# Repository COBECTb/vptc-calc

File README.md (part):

# Калькулятор ВПТК (Волновой редуктор с промежуточными телами качения)

## Сохранённая плата энкодера

Текущая электрическая плата **CAN V2.4 / D70** находится в [electronics/encoder_can_v2](electronics/encoder_can_v2/README.md). Это фиксированный вариант под конкретную геометрию редуктора Ø70 мм, подшипник 40×52×7 мм и фазу сборочных отверстий 39°. Она имеет четыре слоя и толщину 0,8 мм; варианты другой толщины или с двумя слоями не входят в эту ревизию. Размерная привязка и параметры эталонной сборки — [MECHANICAL_VARIANT.md](electronics/encoder_can_v2/MECHANICAL_VARIANT.md).

## Запуск

Основной `calc-vpts.py` создаёт **полный комплект CAD**: сборки, отдельные
печатные детали, библиотеки геометрии и список деталей. Для текущего Ø70:

```sh
python3 calc-vpts.py --resolution 600 --ratio 19 --roller-d 4 --roller-h 5 \
  --rout 28 --diameter 70 --part knee_assembly \
  --output output/generated/robot.scad
```

Требуется Python с `numpy`. Результат:

- `robot.scad` — общий файл; `generated_part` выбирает сборку или деталь;
- `robot_assets/` — все необходимые библиотеки, включая текущую стопу;
- `robot_print/` — **37 отдельных заданий** с названиями деталей;
- `robot_print/README.md` — количество на узел, материалы и порядок сборки;
- `robot.encoder.json` — размеры, совместимость PCB, перечень деталей и хеши файлов.

Все эти файлы генерируются одним запуском. `--part` выбирает начальное отображение,
а не ограничивает состав комплекта. Папки `robot_assets` и `robot_print` должны
переноситься вместе с `robot.scad`; сохранённых STL или моделей из `output` для
работы генератора не требуется. При повторной генерации нужен `--overwrite`;
защищён каждый файл комплекта, включая библиотеки и отдельные задания печати.

Чтобы сразу получить STL всех печатных вариантов, добавить `--export-stl` к команде.
Нужен установленный OpenSCAD; путь можно передать через `--openscad`. Для отдельных
STL добавить, например, `--export-stl --stl-part encoder_magnet_ring_half --stl-part knee_magnet_ring`.
Файлы появятся рядом с соответствующими SCAD. Исходные варианты и запасные детали
включены в каталог отдельно: печатать весь каталог как комплект одной ноги не нужно.
Количество указано **на узел**, а не на всю собаку; `assemblies` в JSON группирует
детали по назначению.

Автоматический экспорт использует двоичный STL и проверяет замкнутость сетки
и направление граней. Численные вырождения экспорта устраняются с округлением
не более 0,00001 мм; если сетка остаётся незамкнутой, экспорт завершается ошибкой.
Подробности рендера и проверки сохраняются в `*_print/.build/`.

Для правок использовать `calc-vpts.py`, `encoder_scad.py` и исходники в
[`cad/`](cad/README.md), затем повторять генерацию. В `cad/` перенесены принятые
модели редуктора V2, колена с двумя опорами полукольца и текущей стопы.
Для штатного Ø70 плата загружается из сохранённых механических данных KiCad V2;
хеш исходной PCB проверяется перед генерацией. Для другого диаметра рассчитывается
механический вариант редуктора; готовая PCB V2 и колено автоматически не масштабируются.

В исходной механике остаётся осевое пересечение ушка тяги и короткого плеча
шарнира на 0,5 мм. Генератор его сохраняет; это нужно исправить до сборки.
Перенос моделей в генератор не является подтверждением прочности или точности энкодера.

Альтернатива — Docker (с OpenSCAD для экспорта STL):

```
docker build -t vptc-calculator .
```

```
docker run --rm -it \
  -v "$(pwd)":/app -w /app \
  vptc-calculator
```

## Описание

Калькулятор генерирует 3D-модель волнового редуктора с роликами (VPTC - Variable Pace Traction Coupling) с параметрами, задаваемыми пользователем. В папку output помещается файл vptc_roller.scad который необходимо открыть в программе OpenSCAD.

Существующие файлы защищены от перезаписи. Для нового результата укажите `--output`,
а для намеренной перезаписи выбранного файла — `--overwrite`.

### Варианты деталей редуктора для установки энкодера

Для установки абсолютного энкодера предусмотрены доработанные варианты
крышки редуктора, зажима соединителей и обоих соединителей, а также защитная
накладка крышки. Плата и носитель магнитов входят в эту сборку как компоненты
энкодера. Исходные модули деталей и режим `legacy` сохранены. Пример без
интерактивного ввода:

```sh
python calc-vpts.py --resolution 600 --ratio 19 --roller-d 4 --roller-h 5 \
  --rout 28 --diameter 70 --part encoder_assembly \
  --output output/encoder_reducer_generated.scad
```

Рядом сохраняется `*.encoder.json`: размеры колец, положение датчиков/крепежа,
контур платы и осевые размеры для будущей генерации платы. Ни один файл ручных
вариантов в `output` генератор не читает и не изменяет.

Доступные значения `--part`:

| Значение | Результат |
| --- | --- |
| `legacy` | Исходная сборка и модули робота |
| `encoder_assembly`, `encoder_section`, `encoder_exploded` | Сборка, разрез, разнесённая сборка |
| `encoder_cap`, `encoder_lid`, `encoder_print` | Крышка редуктора под энкодер, её защитная накладка, обе детали для печати |
| `encoder_clamp`, `encoder_clamp_half` | Доработанный зажим соединителей под энкодер, одна печатная половина |
| `encoder_magnet_ring`, `encoder_clamp_print` | Отдельные половинки кольца со сквозными отверстиями, две половины стоя и обе половинки кольца плашмя |
| `encoder_connector`, `encoder_load_connector` | Выходной соединитель и соединитель нагрузки редуктора, доработанные под энкодер |
| `encoder_pcb` | Механический контур платы |
| `reducer_complete` | Полный редуктор с крышкой V2, сепаратором, подшипниками и соединителями |
| `leg_assembly` | Нога с текущим коленом V2 и стопой; анимация в пределах проверенного хода колена |
| `knee_assembly`, `knee_section`, `knee_exploded` | Сборка колена, разрез и разнесённый вид |
| `knee_mount`, `knee_stage` | Две опоры полукольца и этапы сборки колена |
| `knee_hip`, `knee_lower`, `knee_shin`, `knee_cover`, `knee_magnet_ring` | Печатные детали колена с платой V2 |
| `encoder_magnet_ring_half` | Одна одинаковая половинка кольца редуктора для печати плашмя |
| `foot_rigid`, `foot_sole`, `foot_cuff` | Текущая стопа с зажимом, TPU-накладка и запасной зажим |
| `body_front`, `body_rear`, `body_battery` | Отдельные секции корпуса робота |

В OpenSCAD выбор можно менять переменной `generated_part`. Все варианты редуктора Ø70
по умолчанию используют угол основных отверстий **39°**, чтобы совпасть с текущей
KiCad-платой и взаимно соответствовать в одном комплекте. Явный `--hole-angle` задаёт
свой угол; генератор предупреждает, если готовая плата Ø70 ему не соответствует.

Колено: `animate=false` включает ручное управление `knee_angle`; при `animate=true`
работает OpenSCAD **Вид → Анимировать**. При `$t=0` отображается заданный угол.
Печатные задания не двигаются при анимации. `legacy` сохраняет прежнюю компоновку
робота, заменяя зависимости от внешних STL процедурными модулями; новые колено
и полная нога представлены отдельными режимами.

Количество магнитов выбирается как максимальная чётная пара при перемычке не менее
0,6 мм между посадками Ø5,2. Внутреннее кольцо содержит на одну пару полюсов меньше:
для Ø70 получается **24/26**, для Ø80 — **30/32**. Радиусы, длина шейки и осевой подъём
вычисляются из размеров: в текущем Ø70 сепаратор и подшипник подняты на 0,5 мм,
шейка соединителя имеет длину **6,75 мм**.
Магнитные посадки вынесены в отдельное кольцо толщиной **0,8 мм** со
сквозными отверстиями Ø5,2, которое печатается двумя одинаковыми половинками
плашмя — по одной на каждую половину зажима. Плоский торец полузажима снижен
с Z12 до Z11,6; верхняя стенка стала тоньше на 0,4 мм. Кольцо занимает
Z11,6–12,4, поэтому положение магнитов и длины соединителей сохранены.
Печатаются две одинаковые половины корпуса зажима и две одинаковые половинки
кольца. Половинку приклеивают к торцу своей половины зажима; толщину клеевого
слоя нужно учитывать при установке.
Для отдельной печати одной половинки есть
`output/connector_clamp_magnet_ring_half_0p8.scad` (нужно два экземпляра).
В каждой половинке Ø70 — 12 внутренних и 13 наружных отверстий. Пластик одинаковый,
но полярность первого магнита наружного ряда у второй половинки противоположная;
у внутреннего ряда — одинаковая. Чередование N/S сохраняется через оба стыка.
Произвольный общий поворот собранного зажима учитывается привязкой к известному
положению сустава (упор или сборочный шаблон) с сохранением смещения нуля.
После переустановки зажима эту привязку повторяют. Установочные метки либо
однозначный механический упор полезны для повторяемости сборки; они не заменяют
проверку погрешности энкодера. Неправильную полярность отдельных магнитов одной
поправкой нуля исправить нельзя.
Под максимальный корпус MCU 5,1×5,1 мм предусмотрен локальный карман с зазором
0,2 мм по сторонам и 0,15 мм снизу. Для Ø70 дно кармана находится на Z10,25,
выше неизменённого подшипникового упора Z10.

Для штатного Ø70 генератор использует контур, два крепления и компоненты
разведённой компактной платы V2 (`electronics/encoder_can_v2`). Механические данные
читаются из `design/mechanics_v2.json`; хеш проверяется по сохранённой PCB.
Экспорт обновляется `scripts/export_mechanics.py` через Python KiCad.
Актуальная воспроизводимая сборка крышки — режим `encoder_assembly` основного генератора.
Сохранённый прежний файл: `output/reducer_cap_encoder_can.scad`.
Для других диаметров плата в генерируемом SCAD остаётся механическим макетом.
Другой диаметр или расположение отверстий требует новой электрической разводки. Подъём сепаратора ещё требует
проверки его окон роликов и сопряжения с 688ZZ в полной сборке редуктора.
У открытых поверхностей вычитания выступают на 0,01 мм; глухие глубины и упор
подшипника сохранены.

Проверки генератора: `python -m unittest discover -s tests -v`. Если установлен
OpenSCAD, они также проверяют компиляцию всех новых вариантов Ø70/Ø80 и реальную
геометрию упора подшипника, дна потая и локального кармана MCU.
Путь CLI можно задать переменной `OPENSCAD`.

## Генерируемые детали

Иллюстрированный каталог ниже показывает **29 ранее сохранённых деталей**.
Актуальный полный перечень, включая колено V2 и отдельные полукольца, создаётся
в `*_print/README.md` основным генератором.
На каждой картинке — геометрия соответствующего модуля OpenSCAD, а не эскиз.
Слева объёмный вид, справа вид вдоль локальной оси Z. Масштаб видов подбирается
отдельно; габарит XYZ указан под изображением. Размеры — в миллиметрах, углы — в градусах.

### Как получить и открыть отдельную деталь

Для каждой детали есть готовый файл в [docs/parts](docs/parts), который вызывает
ровно один модуль и скрывает остальную сборку. Ссылка «Открыть деталь» дана
в каждой карточке. Открыть этот `.scad` в OpenSCAD, нажать **F5** для просмотра,
**F6** для точного рендера, затем **Файл → Экспорт → STL**. Положение для
печати отдельно задано только там, где вызван модуль с суффиксом `_print`.

Картинки и файлы карточек используют сохранённый
[эталонный результат генератора](docs/parts/reference_model.scad):

```sh
python3 calc-vpts.py --resolution 600 --ratio 19 --roller-d 4 --roller-h 5 \
  --rout 28 --diameter 70 --hole-angle 39 --part encoder_assembly \
  --output output/my_reducer.scad
```

Для собственной версии создать рядом с результатом небольшой файл, например
`output/my_cap.scad`:

```scad
use <my_reducer.scad>
$fn=60;
cap();
```

Вместо `cap();` подставить вызов из нужной карточки. Для текущей стопы и TPU-опоры
использовать задания `foot_rigid.scad` и `foot_sole.scad` из созданного каталога `*_print/`.

### Где изменять параметры

| Уровень | Что менять | Когда пересчитывается |
| --- | --- | --- |
| CLI генератора | `--resolution`, `--ratio`, `--roller-d`, `--roller-h`, `--rout`, `--diameter`, `--hole-angle` | Повторным запуском `calc-vpts.py` с новым `--output` |
| Аргументы модулей | Например, `reducer_connector(h1=8,skirt=true)` или `shin(foot=false)` | Сразу при F5/F6 в файле отдельной детали |
| Переменные SCAD | Толщины, высоты, зазоры и размеры посадок в сгенерированном файле | После изменения самого файла, из которого импортируется модуль |
| Библиотека стопы | Переменные `h_*` в `cad/foots_h.scad` | После повторного запуска генератора |

**Профиль впадин, число роликов, координаты отверстий и часть размеров записываются
Python как готовые числа.** Одной замены `D_out` или `d_roller` в SCAD недостаточно:
для другой передачи или диаметра нужно повторно запустить генератор.
Переменные из файла, подключённого через `use`, не становятся переменными внешнего
файла: менять их нужно в исходном SCAD, а через вызов передавать только его аргументы.
Значения в таблицах ниже относятся к указанному эталону Ø70; это не универсальные
размеры для всех диаметров. Исходный генератор и его формулы — [calc-vpts.py](calc-vpts.py),
параметры доработок редуктора под энкодер — [encoder_scad.py](encoder_scad.py).

### Редуктор

#### 1. Жёсткое колесо / корпус

[Открыть деталь](docs/parts/rigid_gear.scad) · Источник: [reference_model.scad](docs/parts/reference_model.scad).

Вызов для отдельного файла:

```scad
rigid_gear();
```

Как построить: Создать цилиндр корпуса. Выдавить рассчитанный Python профиль впадин и вычесть его сверху. Вырезать отверстия A/B и ступенчатую посадку 6803ZZ.

| Параметр | Значение в эталоне | Что задаёт |
| --- | --- | --- |
| `D_out` | 70 | Наружный диаметр, из --diameter |
| `h_reducer` | 15.5 | Высота корпуса: h_roller + 10.5 |
| `h_cut` | 10 | Глубина профильной полости: h_roller + 5 |
| `--ratio / --resolution` | 19 / 600 | 20 впадин и число точек рассчитанного профиля |
| `motor_radius / motor_angles` | 32 / [54,144,234,324]° | Расположение отверстий B |

#### 2. Корпус с боковым креплением

[Открыть деталь](docs/parts/rigid_gear_with_bracing.scad) · Источник: [reference_model.scad](docs/parts/reference_model.scad).

Вызов для отдельного файла:

```scad
rigid_gear_with_bracing();
```

Как построить: Взять rigid_gear(). Добавить боковой объём, двумя овальными конусами сформировать выемки, повторно прорезать отверстия B и отверстия бокового крепления.

| Параметр | Значение в эталоне | Что задаёт |
| --- | --- | --- |
| `bracing_offset_y` | 29 | Смещение крепления: D_out/2 − 6 |
| `bracing_offset_z` | 17.5 | Высота оси крепления: D_out/4 |
| `bracing_offset_x` | 2.2 | Значение в сгенерированном SCAD; 2.25 в Python округляется до одного знака |
| `side_long / side_short` | 29.564 / 12.246 | Расстояния между боковыми отверстиями |

#### 3. Сепаратор

[Открыть деталь](docs/parts/separator.scad) · Источник: [reference_model.scad](docs/parts/reference_model.scad).

Вызов для отдельного файла:

```scad
separator();
```

Как построить: Создать цилиндр Rsep_out, вычесть внутреннюю полость Rsep_in. Сделать ступени фланца, посадку 688ZZ, радиальные окна под ролики и восемь крепёжных отверстий.

| Параметр | Значение в эталоне | Что задаёт |
| --- | --- | --- |
| `Rsep_m` | 25.2 | Радиус центров роликов |
| `Rsep_out / Rsep_in` | 26.08 / 24.32 | Наружный и внутренний радиусы сепаратора |
| `separator_h` | 9 | Основная высота: h_roller + 4 |
| `bearing_inner / bearing_outer` | 40 / 52 | Посадка выбранного 6808-2RS |
| `--ratio / h_roller` | 19 / 5 | Число окон / высота роликов |

#### 4. Ролики

[Открыть деталь](docs/parts/rollers.scad) · Источник: [reference_model.scad](docs/parts/reference_model.scad).

Вызов для отдельного файла:

```scad
rollers();
```

Как построить: Построить цилиндр ролика с центром по Z. Разместить 19 копий на окружности Rsep_m поворотами с шагом 360/19.

| Параметр | Значение в эталоне | Что задаёт |
| --- | --- | --- |
| `d_roller / h_roller` | 4 / 5 | Диаметр / высота, из --roller-d и --roller-h |
| `Rsep_m` | 25.2 | Радиус расположения |
| `--ratio` | 19 | Количество роликов; пересчитывается в Python |

#### 5. Эксцентрик

[Открыть деталь](docs/parts/eccentric.scad) · Источник: [reference_model.scad](docs/parts/reference_model.scad).

Вызов для отдельного файла:

```scad
eccentric();
```

Как построить: Создать диск радиуса rd. Вырезать проход Ø24 и посадку под 6803ZZ Ø26, оставив нижний упор. Смещение оси задаётся при установке детали в сборку.

| Параметр | Значение в эталоне | Что задаёт |
| --- | --- | --- |
| `rd` | 23.2 | Радиус диска; вычисляется и записывается в геометрию |
| `eccentric_h` | 7 | Толщина: h_roller + 2 |
| `eccentricity` | 0.8 | Смещение в сборке: 0.2 × d_roller |
| `посадка 6803ZZ` | Ø26 × 5 | Геометрия подшипника; Ø24 у нижнего упора |

#### 6. Вал эксцентрика

[Открыть деталь](docs/parts/eccentric_shaft.scad) · Источник: [reference_model.scad](docs/parts/reference_model.scad).

Вызов для отдельного файла:

```scad
eccentric_shaft();
```

Как построить: Объединить цилиндры основания, проставки, смещённой ступени и верхнего шипа. Вырезать осевое отверстие и два нижних паза.

| Параметр | Значение в эталоне | Что задаёт |
| --- | --- | --- |
| `ecc_shaft_h1` | 5 | Высота нижней ступени |
| `ecc_spacer_h` | 2.5 | Высота проставки |
| `ecc_shaft_h2` | 6 | Высота смещённой ступени |
| `ecc_pin_h` | 6 | Высота шипа Ø8 |
| `eccentricity` | 0.8 | Смещение средней ступени по X |

#### 7. Крышка редуктора

[Открыть деталь](docs/parts/cap.scad) · Источник: [reference_model.scad](docs/parts/reference_model.scad).

Вызов для отдельного файла:

```scad
cap();
```

Как построить: Создать диск D_out. Вырезать посадку наружного кольца подшипника, сквозное отверстие меньшего диаметра, нижнюю полость под сепаратор и отверстия A с потаями.

| Параметр | Значение в эталоне | Что задаёт |
| --- | --- | --- |
| `cap_thickness` | 11 | Общая толщина |
| `bearing_outer` | 52 | Диаметр посадки 6808-2RS |
| `bearing_width` | 7 | Ширина выбранного подшипника |
| `Rsep_out` | 26.08 | Радиус нижней полости = Rsep_out + 1 |
| `--hole-angle` | авто / 39° для энкодера Ø70 | Фаза группы A задаётся при генерации |

#### 8. Крышка с боковым креплением

[Открыть деталь](docs/parts/cap_with_bracing.scad) · Источник: [reference_model.scad](docs/parts/reference_model.scad).

Вызов для отдельного файла:

```scad
cap_with_bracing();
```

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
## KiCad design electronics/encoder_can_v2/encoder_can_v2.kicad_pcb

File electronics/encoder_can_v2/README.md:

# Энкодер CAN V2.4 — вариант для редуктора D70

**Сохранённый размерный вариант: `encoder_can_v2_4_d70`.** Эта готовая плата рассчитана на конкретную сборку ВПТК Ø70 мм: подшипник 40×52×7 мм, основные отверстия на R31,5 мм с фазой 39°, магнитные дорожки R23,5/R29,5 мм. Для другого редуктора совместимость определяется повторной проверкой геометрии; изменение диаметра в калькуляторе не масштабирует готовую разводку. Полная привязка и параметры воспроизведения — [MECHANICAL_VARIANT.md](MECHANICAL_VARIANT.md).

Открыть `encoder_can_v2.kicad_pro` в KiCad 10. Четыре слоя, 0,8 мм; возвращён **точный исходный узкий контур**, до расширения под отступ 1 мм. Габарит в локальной радиально-поперечной системе **16,853 × 42,938 мм**, площадь контура до вычитания крепёжных NPTH **395,29 мм²**. Наружный радиус 33,4 мм. Все 826 отрезков Edge.Cuts независимо сверены с сохранённой исходной платой.

**U2/U3 не перемещались:** центры KiCad (123,2666;95,9099) и (129,1928;94,9713) мм, ориентация 9°. Активные точки рассчитаны на кольца R23,5/R29,5 мм. J2 также сохранён. Монтажные отверстия PCB в локальных координатах (26,92;−9,605) и (28,1933;9,6043) мм. Оба доступа к сборочным M3 — открытые вырезы; замкнутых внутренних окон контура нет. Актуальный контур и крепления передаются в OpenSCAD.

F.Cu: Hall, CAN, защита и LDO. In1.Cu: один связный полигон GND без сигнальных дорожек. In2.Cu: 3,3 В и сигналы. B.Cu: MCU, кварц, LED, пассивные детали и клипса. Минимальные дорожка/зазор 0,127 мм, переходы 0,4/0,2 и 0,45/0,2 мм. Все переходы сквозные, закрыты маской с обеих сторон. Номинальный минимальный отступ от края меди перехода до любой паяемой площадки обеих сторон, включая свою цепь и J1/J2, — **0,505 мм** (требование ≥0,5 мм). Под максимальными корпусами переходов нет; минимальный номинальный зазор до корпуса 0,125 мм. 14 прямых выходов MCU чередуются по длине: 11 реальных межслойных переходов и 3 поворота на той же стороне без лишнего отверстия. Изготовительные допуски не включены в эту номинальную величину.

Питание: стабилизированные **5 В**. J1: 1 +5 В, 2 GND, 3 CANH, 4 CANL; ручная пайка проводов. J2 на B.Cu: **+5 В вход, GND, SWDIO, SWCLK, NRST**, 5 площадок P2.54. Pin1 не VTREF; логика SWD 3,3 В. Программировать до установки платы в корпус. Подробности — [PROGRAMMING.md](PROGRAMMING.md).

STM32G431KBU6, два TMAG5273A2QDBVR на независимых I²C, TCAN332GDCNR, TPS7A2033PDBVR. D1 — защита CAN PESD5V0S2BT,215. Кварц — точный ABM10-16.000MHZ-12-R80-3-D30-T. R9 120 Ом по умолчанию DNP, устанавливается только на двух концах всей шины.

D2 зелёный — питание 3,3 В, D3 жёлтый — команды, D4 красный — фаза. Последние два управляются PA4/PA5; прошивка индикаторов ещё требуется. Корпуса Kingbright APG1005 ограничены высотой 0,3 мм. Прозрачные световоды редуктора Ø0,6 мм в каналах Ø0,8 мм — опытная конструкция: изготовление и яркость требуют пробной сборки. В колене LED видны через отверстия крышки.

Под головками M2 нет наружной меди в Ø4,4 мм. Крепёж платы: **M2×5, головка не больше Ø3,8×1,3 мм, без шайбы**. Минимальный номинальный запас головки до края PCB с учётом люфта стержня — 0,7557 мм. Для сборочных M3 ISO10642 предусмотрен потай Ø7,1 мм под головку до Ø6,72×1,86 мм; длина винта выбирается по фактической полной сборке.

Механика генерируется из `calc-vpts.py`, актуальной сохранённой PCB и `cad/`, без использования старых STL. Пакет генератора содержит все печатные детали и установки платы в редукторе и колене. Для других диаметров генерация механики параметрическая; готовая электрическая PCB V2.4 рассчитана на текущую геометрию D70 и не масштабируется автоматически.

Подробной 3D-модели MCU в KiCad нет; при проверке установки OpenSCAD использует его максимальный габарит. Это не отсутствие компонента в BOM или монтаже.

Текущие проверки и условия передачи в производство — [ORDER_READINESS.md](ORDER_READINESS.md). Архив KiCad содержит местные библиотеки, STEP-модели, BOM, координаты и отчёты; в копии меняются только ссылки на модели. Производственные файлы предназначены для опытной партии. Подтверждённой точности угла, запуска кварца, теплового режима и работы всей CAN-сети без собранного образца нет.

Источник PCB SHA256: `43237adbcdb743c33c8f1bdc61387ee4b917825291ee4f41e4ae68c7d174684c`.

Шелкография V2.4: печатаемые штрихи не тоньше 0,15 мм, видимый текст не ниже 1 мм. Необязательные рамки неполярных 0402 убраны; pin 1 и обозначения Hall сохранены. Проверка учитывает опубликованные ограничения Резонит; заводское согласование стека, панели и процесса остаётся отдельным условием.

Очистка V2.4: убраны лишние петли и мелкие изломы. Сравнения до/после — `design/cleanup_details_1.png`–`cleanup_details_3.png`; реальная открытая медь — `design/mask_review.png`. Обязательная центральная паяемая площадка GND STM32 сохранена. Подробности — [design/cleanup_review.md](design/cleanup_review.md).

У U1 убран обход GND16 вокруг питания15 к GND14: оба земляных контакта подключены внутрь к EP33. Сравнение — `design/u1_ground_review.png`.

Вход внешней GND в контакт14 U1 выровнен по центру площадки; выступ над площадкой убран. Сравнение — `design/u1_entry_review.png`.

Последние зелёные правки применены: R5/BOOT0, подвод C8, ствол питания C4/C5/U2. См. `design/green_marks_review.png` и `design/green_marks_front_back.png`.

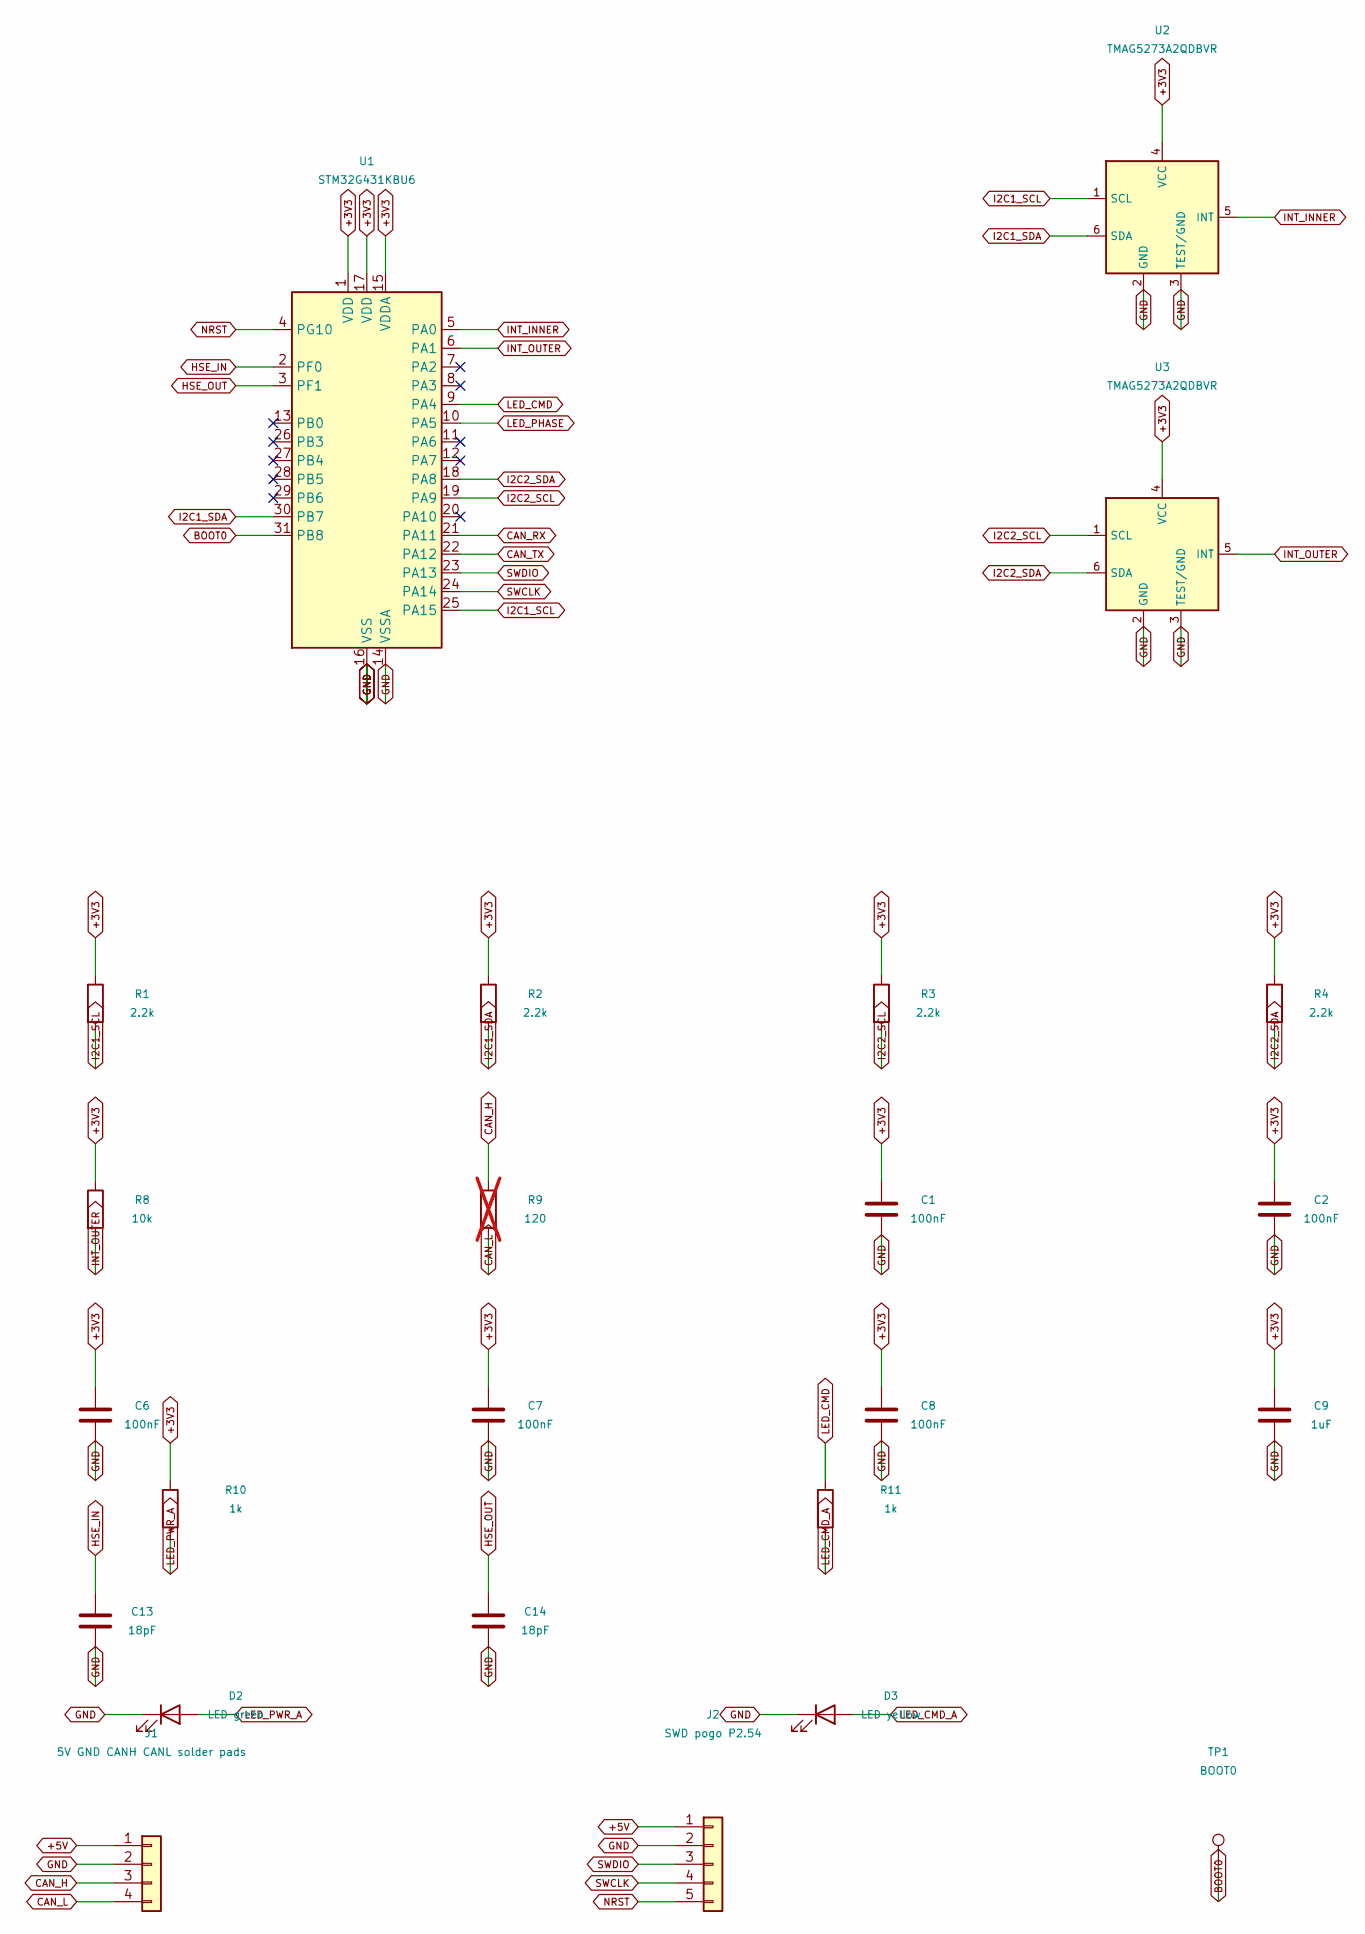
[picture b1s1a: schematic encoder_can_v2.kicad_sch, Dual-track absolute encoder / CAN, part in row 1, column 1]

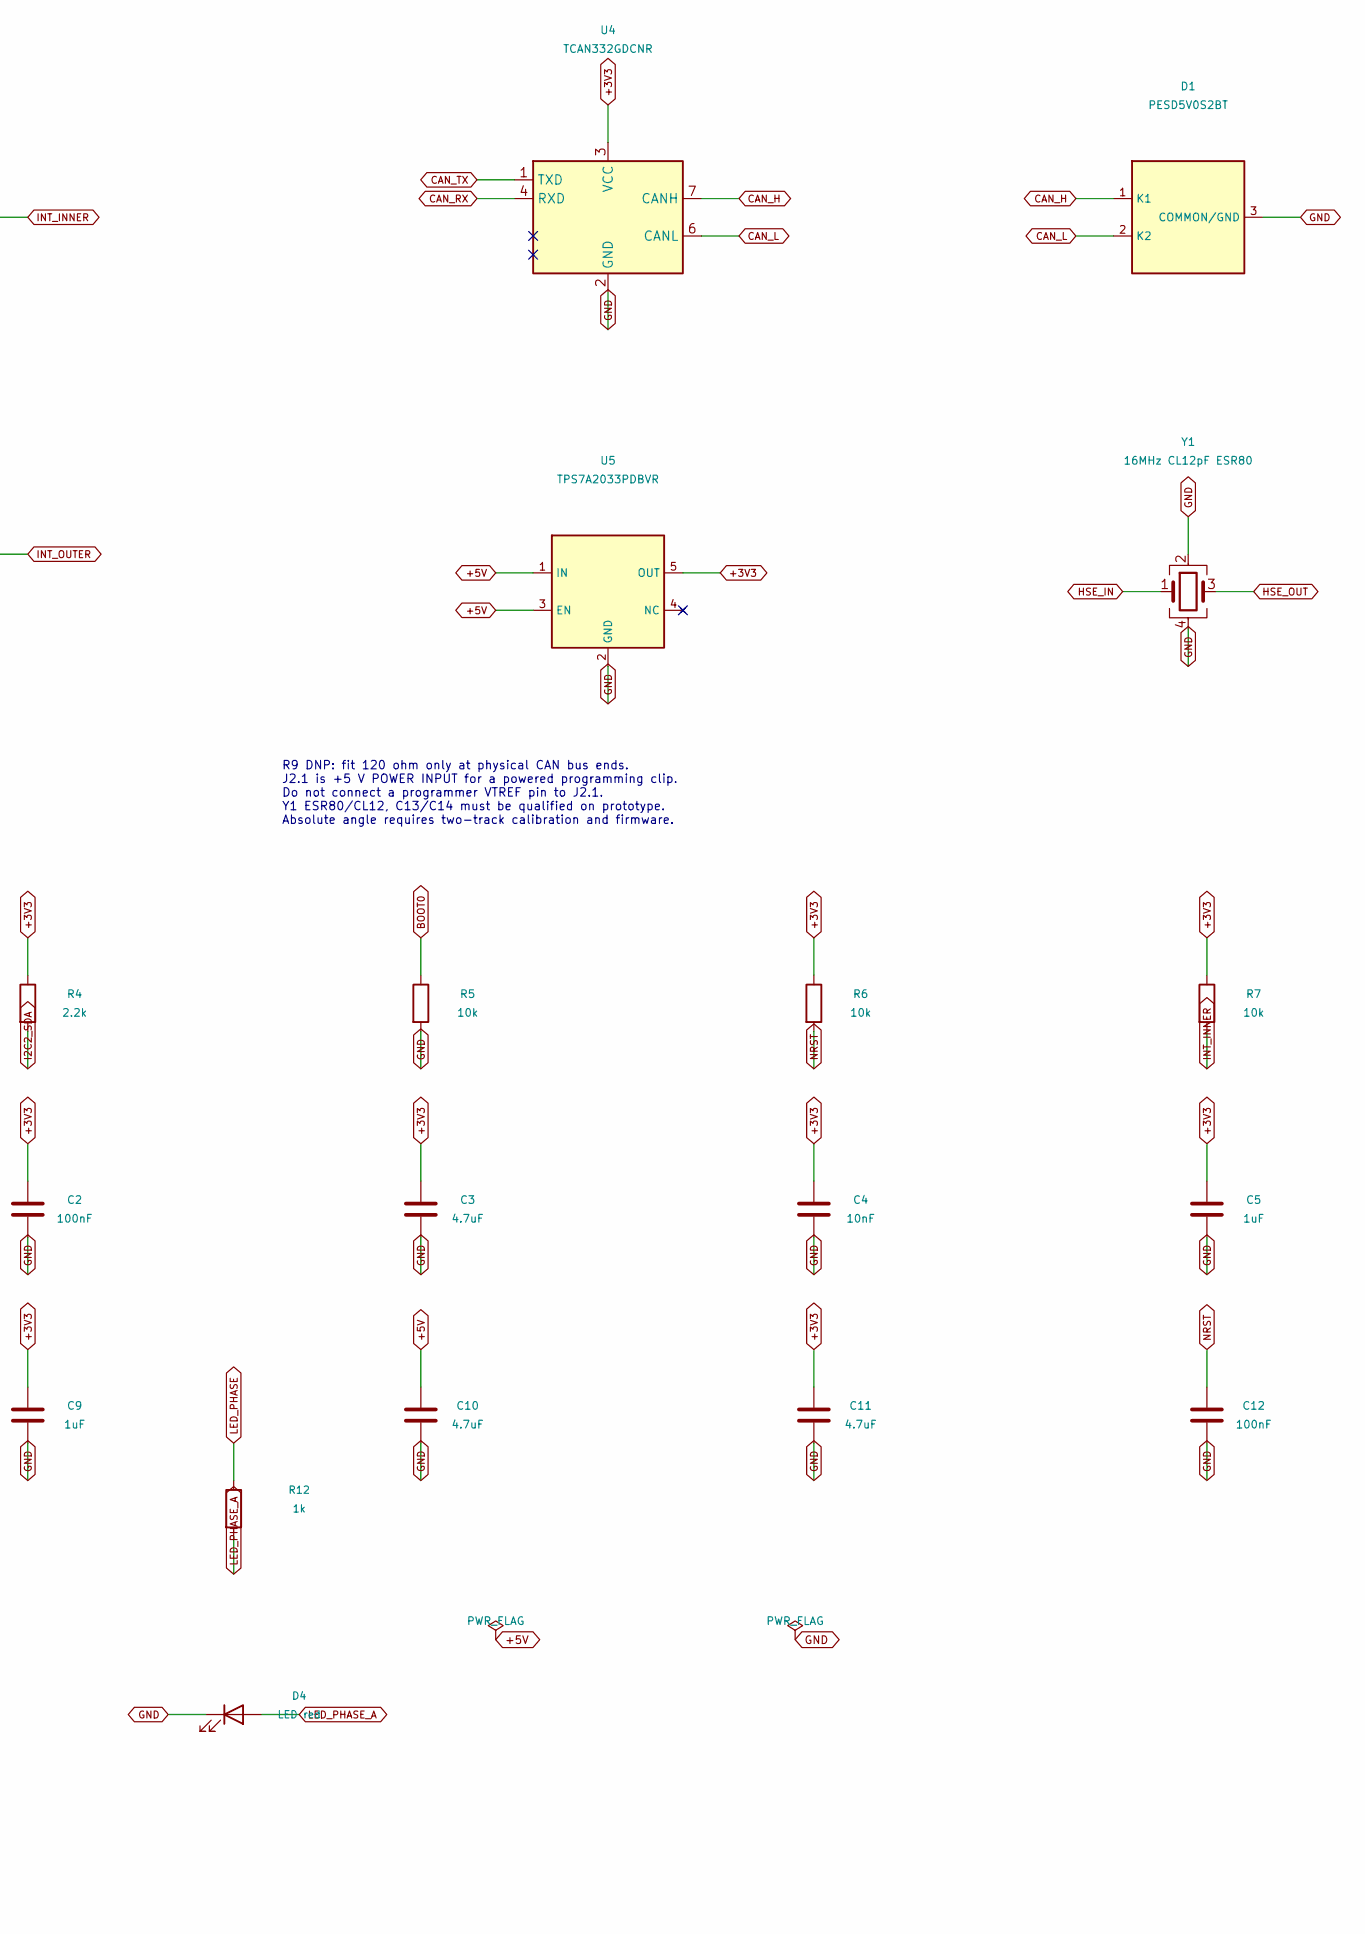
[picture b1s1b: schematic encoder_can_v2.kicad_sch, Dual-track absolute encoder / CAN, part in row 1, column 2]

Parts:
C1, C2, C6, C7, C8, C12: 100nF; C_0402_1005Metric; MPN GRM155R71C104KA88D
C3, C10, C11: 4.7uF; C_0603_1608Metric; MPN GRM188R61C475KE11D
C4: 10nF; C_0402_1005Metric; MPN GRM155R71H103KA88D
C5, C9: 1uF; C_0402_1005Metric; MPN GRM155R61E105KA12D
C13, C14: 18pF; C_0402_1005Metric; MPN GRM1555C1H180JA01D
D1: PESD5V0S2BT; SOT-23_TVS_CompactCourtyard; MPN PESD5V0S2BT,215
D2: LED green; LED_Kingbright_APG1005; MPN APG1005CGC-T
D3: LED yellow; LED_Kingbright_APG1005; MPN APG1005SYC-T
D4: LED red; LED_Kingbright_APG1005; MPN APG1005SEC/E-T
J1: 5V GND CANH CANL solder pads; WirePads_1x04
J2: SWD pogo P2.54; SWD_Pogo_1x05_P2.54mm
R1, R2, R3, R4: 2.2k; R_0402_1005Metric; MPN RC0402FR-072K2L
R5, R6, R7, R8: 10k; R_0402_1005Metric; MPN RC0402FR-0710KL
R9: 120; R_0603_1608Metric; MPN RC0603FR-07120RL; not fitted
R10, R11, R12: 1k; R_0402_Status; MPN RC0402FR-071KL
TP1: BOOT0; TestPoint_Pad_D1.0mm
U1: STM32G431KBU6; STM32G431KBU6_UFQFPN32; MPN STM32G431KBU6
U2, U3: TMAG5273A2QDBVR; TMAG5273_DBV_TI; MPN TMAG5273A2QDBVR
U4: TCAN332GDCNR; SOT-23-8; MPN TCAN332GDCNR
U5: TPS7A2033PDBVR; SOT-23-5; MPN TPS7A2033PDBVR
Y1: 16MHz CL12pF ESR80; Crystal_SMD_2520-4Pin_2.5x2.0mm; MPN ABM10-16.000MHZ-12-R80-3-D30-T

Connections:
+3V3: C1.1, C2.1, C3.1, C4.1, C5.1, C6.1, C7.1, C8.1, C9.1, C11.1, R1.1, R2.1, R3.1, R4.1, R6.1, R7.1, R8.1, R10.1, U1.1 (VDD), U1.15 (VDDA), U1.17 (VDD), U2.4 (VCC), U3.4 (VCC), U4.3 (VCC), U5.5 (OUT)
+5V: C10.1, J1.1, J2.1, U5.1 (IN), U5.3 (EN)
BOOT0: R5.1, TP1.1, U1.31 (PB8)
CAN_H: D1.1 (K1), J1.3, R9.1, U4.7 (CANH)
CAN_L: D1.2 (K2), J1.4, R9.2, U4.6 (CANL)
CAN_RX: U1.21 (PA11), U4.4 (RXD)
CAN_TX: U1.22 (PA12), U4.1 (TXD)
GND: C1.2, C2.2, C3.2, C4.2, C5.2, C6.2, C7.2, C8.2, C9.2, C10.2, C11.2, C12.2, C13.2, C14.2, D1.3 (COMMON/GND), D2.1 (K), D3.1 (K), D4.1 (K), J1.2, J2.2, R5.2, U1.14 (VSSA), U1.16 (VSS), U1.32 (VSS), U1.33 (VSS), U2.2 (GND), U2.3 (TEST/GND), U3.2 (GND), U3.3 (TEST/GND), U4.2 (GND), U5.2 (GND), Y1.2, Y1.4
HSE_IN: C13.1, U1.2 (PF0), Y1.1
HSE_OUT: C14.1, U1.3 (PF1), Y1.3
I2C1_SCL: R1.2, U1.25 (PA15), U2.1 (SCL)
I2C1_SDA: R2.2, U1.30 (PB7), U2.6 (SDA)
I2C2_SCL: R3.2, U1.19 (PA9), U3.1 (SCL)
I2C2_SDA: R4.2, U1.18 (PA8), U3.6 (SDA)
INT_INNER: R7.2, U1.5 (PA0), U2.5 (INT)
INT_OUTER: R8.2, U1.6 (PA1), U3.5 (INT)
LED_CMD: R11.1, U1.9 (PA4)
LED_CMD_A: D3.2 (A), R11.2
LED_PHASE: R12.1, U1.10 (PA5)
LED_PHASE_A: D4.2 (A), R12.2
LED_PWR_A: D2.2 (A), R10.2
NRST: C12.1, J2.5, R6.2, U1.4 (PG10)
SWCLK: J2.4, U1.24 (PA14)
SWDIO: J2.3, U1.23 (PA13)

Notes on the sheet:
R9 DNP: fit 120 ohm only at physical CAN bus ends. J2.1 is +5 V POWER INPUT for a powered programming clip. Do not connect a programmer VTREF pin to J2.1. Y1 ESR80/CL12, C13/C14 must be qualified on prototype. Absolute angle requires two-track calibration and firmware.

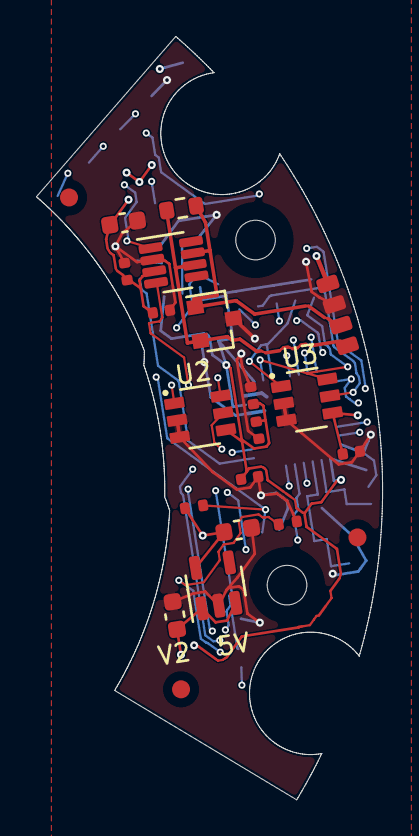
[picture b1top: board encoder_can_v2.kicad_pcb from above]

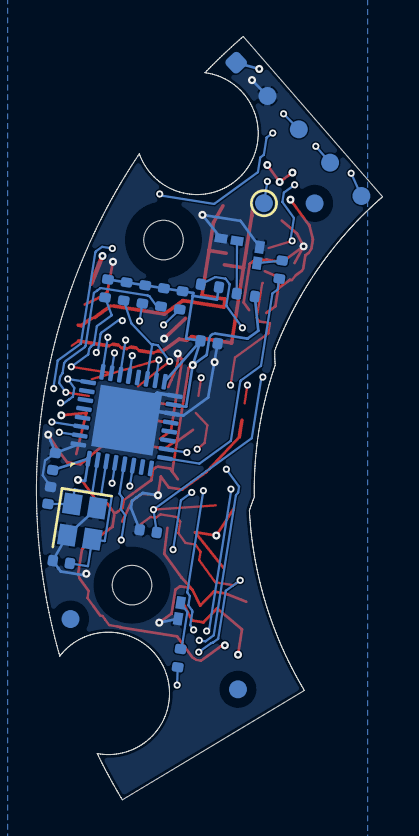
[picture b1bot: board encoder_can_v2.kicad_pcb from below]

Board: 4 copper layers, 19.2 x 42.4 mm, 47 parts (24 on the bottom side), 24 nets.

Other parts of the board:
FIDB1, FIDB2, FIDB3: Fiducial_1mm_Mask2mm
FIDF1, FIDF2, FIDF3: Fiducial_1mm_Mask2mm
H1, H2: MountingHole_2.2mm_M2; MountingHole_2.2mm_M2_LowHead

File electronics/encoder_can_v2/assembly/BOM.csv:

References,Quantity_per_board,Fitted_quantity_per_board,Value,Footprint,Manufacturer,MPN,Populate,Supplier_stock_code,Supplier,Procurement_status,Requirements
U1,1,1,STM32G431KBU6,Encoder_CAN:STM32G431KBU6_UFQFPN32,STMicroelectronics,STM32G431KBU6,Yes,C529358,LCSC,exact MPN selected; retail distributor stock observed; assembler inventory/reservation not implied,"Pin33 is KiCad EP pad numbering, not an extra perimeter lead.; No separate VBAT, VREF+, VCAP pins in this package.; VREFBUF must remain disabled because VREF+ is bonded to VDDA.; NRST remains reset input; do not configure as GPIO.; Keep SWD enabled; PA15 can become I2C1 SCL while PA13/PA14 retain SWD.; Footprint uses KiCad 10.0.6 UFQFPN32 IPC outer lands: radial center 2.4375 mm, 0.875 x 0.25 mm, pitch 0.5 mm. EP is 3.45 x 3.45 mm per ST Figure 41; adapted IPC pattern, not a literal copy of Figure 41.; maximum body height mm: 0.6"
"U2, U3",2,2,TMAG5273A2QDBVR,Encoder_CAN:TMAG5273_DBV_TI,Texas Instruments,TMAG5273A2QDBVR,Yes,C3715882,LCSC,exact MPN selected; retail distributor stock observed; assembler inventory/reservation not implied,"Official TI DBV0006A-C02 land pattern; Hall local footprint offset (-0.12,+0.40) mm. Height from seating plane 0.9 to 1.4 mm.; maximum body height mm: 1.4"
U4,1,1,TCAN332GDCNR,Package_TO_SOT_SMD:SOT-23-8,Texas Instruments,TCAN332GDCNR,Yes,C191007,LCSC,exact MPN selected; retail distributor stock observed; assembler inventory/reservation not implied,TCAN332 has neither standby nor shutdown pin; pins5/8 must be explicitly NC.; Bus absolute maximum is +/-14 V; do not substitute high-standoff automotive TVS and claim coordinated surge protection.; maximum body height mm: 1.45
U5,1,1,TPS7A2033PDBVR,Package_TO_SOT_SMD:SOT-23-5,Texas Instruments,TPS7A2033PDBVR,Yes,C2862740,LCSC,exact MPN selected; retail distributor stock observed; assembler inventory/reservation not implied,IN and EN maximum operating6 V; supply only regulated5 V.; Minimum effective COUT0.47 uF after voltage/temperature/tolerance derating.; Thermal qualification required in closed housing;300 mA rating is not a board operating-current target.; maximum body height mm: 1.45
D1,1,1,PESD5V0S2BT,Encoder_CAN:SOT-23_TVS_CompactCourtyard,Nexperia,"PESD5V0S2BT,215",Yes,C49338,LCSC,exact MPN selected; retail distributor stock observed; assembler inventory/reservation not implied,"Bidirectional +/-5 V standoff;10 V maximum clamp at1 A8/20 us,14 V at12 A.; Limits permissible CAN common-mode to about+/-5 V; shared GND is mandatory.; Transient overshoot depends on layout; this design has no certified ESD/surge immunity.; maximum body height mm: 1.1"
Y1,1,1,16MHz CL12pF ESR80,Crystal:Crystal_SMD_2520-4Pin_2.5x2.0mm,Abracon,ABM10-16.000MHZ-12-R80-3-D30-T,Yes,8063649242,ЧИП и ДИП,"Exact MPN catalogued at ChipDip 2026-10-24: MOQ1, 7–8weeks, from10 130RUB/each; no stock in Moscow shops; not reserved. Alternative8070563644 MOQ269,4weeks.","Pin1 determined by package marking/top view, not chamfer; validate supplier drawing and oscillator gain/drive before assembly release.; Load capacitors18 pF are starting values for CL12 pF and estimated3 pF stray capacitance; tune/verify startup across temperature and rails.; Exact complete MPN verified in DigiKey catalog; custom R80 option already stocked.; Body height max 0.70 mm (0.5 +0.2/-0.1), not 0.50 mm.; 1/3 crystal; 2/4 grounded case; no automatic ESR150 substitute.; maximum body height mm: 0.7; Exact R80 version; 16MHz, CL12pF, ESR<=80ohm; ESR150 is not an approved substitution"
"R1, R2, R3, R4",4,4,2.2k,Resistor_SMD:R_0402_1005Metric,YAGEO,RC0402FR-072K2L,Yes,C114762,LCSC,exact MPN selected; retail distributor stock observed; assembler inventory/reservation not implied,rated voltage V: 50; tolerance %: 1; rated power W: 0.0625; maximum body height mm: 0.4
"R5, R6, R7, R8",4,4,10k,Resistor_SMD:R_0402_1005Metric,YAGEO,RC0402FR-0710KL,Yes,C60490,LCSC,exact MPN selected; retail distributor stock observed; assembler inventory/reservation not implied,rated voltage V: 50; tolerance %: 1; rated power W: 0.0625; maximum body height mm: 0.4
R9,1,0,120,Resistor_SMD:R_0603_1608Metric,YAGEO,RC0603FR-07120RL,No,C114640,LCSC,exact MPN selected; retail distributor stock observed; assembler inventory/reservation not implied,Default DNP. Fit only if this board is a physical bus end. Use0.1 W minimum and qualify bus fault power.; rated voltage V: 75; tolerance %: 1; rated power W: 0.1; maximum body height mm: 0.55
"C1, C2, C6, C7, C8, C12",6,6,100nF,Capacitor_SMD:C_0402_1005Metric,Murata,GRM155R71C104KA88D,Yes,C71629,LCSC,exact MPN selected; retail distributor stock observed; assembler inventory/reservation not implied,dielectric: X7R; rated voltage V: 16; tolerance %: 10; maximum body height mm: 0.55
"C3, C10, C11",3,3,4.7uF,Capacitor_SMD:C_0603_1608Metric,Murata,GRM188R61C475KE11D,Yes,C77045,LCSC,exact MPN selected; retail distributor stock observed; assembler inventory/reservation not implied,dielectric: X5R; rated voltage V: 16; tolerance %: 10; maximum body height mm: 0.95
C4,1,1,10nF,Capacitor_SMD:C_0402_1005Metric,Murata,GRM155R71H103KA88D,Yes,C77019,LCSC,exact MPN selected; retail distributor stock observed; assembler inventory/reservation not implied,dielectric: X7R; rated voltage V: 50; tolerance %: 10; maximum body height mm: 0.55
"C5, C9",2,2,1uF,Capacitor_SMD:C_0402_1005Metric,Murata,GRM155R61E105KA12D,Yes,C77009,LCSC,exact MPN selected; retail distributor stock observed; assembler inventory/reservation not implied,dielectric: X5R; rated voltage V: 25; tolerance %: 10; maximum body height mm: 0.55
"C13, C14",2,2,18pF,Capacitor_SMD:C_0402_1005Metric,Murata,GRM1555C1H180JA01D,Yes,C33149,LCSC,exact MPN selected; retail distributor stock observed; assembler inventory/reservation not implied,dielectric: C0G; rated voltage V: 50; tolerance %: 5; maximum body height mm: 0.55; Initial HSE load value; characterize startup/frequency/drive on prototype
J1,1,0,5V GND CANH CANL solder pads,Encoder_CAN:WirePads_1x04,,,No,,,PCB only; do not order,
J2,1,0,SWD pogo P2.54,Encoder_CAN:SWD_Pogo_1x05_P2.54mm,,,No,,,PCB only; do not order,
TP1,1,0,BOOT0,TestPoint:TestPoint_Pad_D1.0mm,,,No,,,PCB only; do not order,
D2,1,1,LED green,Encoder_CAN:LED_Kingbright_APG1005,Kingbright,APG1005CGC-T,Yes,,,Catalogued internationally; exact low-profile MPN required. Assembler must confirm delivery/reservation.,"Top-emitting ultra-thin LED; pin1 cathode. 1k series resistor; nominal current about 1.3mA, actual brightness to be checked on prototype.; Maker land pattern 0.7x0.5 mm, inner gap0.2 mm; stencil80% area, 80–100 um recommendation; cathode pad1. Max2 reflow passes.; maximum body height mm: 0.3"
D3,1,1,LED yellow,Encoder_CAN:LED_Kingbright_APG1005,Kingbright,APG1005SYC-T,Yes,,,Catalogued internationally; exact low-profile MPN required. Assembler must confirm delivery/reservation.,"Top-emitting ultra-thin LED; pin1 cathode. 1k series resistor; nominal current about 1.3mA, actual brightness to be checked on prototype.; Maker land pattern 0.7x0.5 mm, inner gap0.2 mm; stencil80% area, 80–100 um recommendation; cathode pad1. Max2 reflow passes.; maximum body height mm: 0.3"
D4,1,1,LED red,Encoder_CAN:LED_Kingbright_APG1005,Kingbright,APG1005SEC/E-T,Yes,,,Catalogued internationally; exact low-profile MPN required. Assembler must confirm delivery/reservation.,"Top-emitting ultra-thin LED; pin1 cathode. 1k series resistor; nominal current about 1.3mA, actual brightness to be checked on prototype.; Maker land pattern 0.7x0.5 mm, inner gap0.2 mm; stencil80% area, 80–100 um recommendation; cathode pad1. Max2 reflow passes.; maximum body height mm: 0.3"
"R10, R11, R12",3,3,1k,Encoder_CAN:R_0402_Status,YAGEO,RC0402FR-071KL,Yes,,,Exact resistor MPN; assembler sourcing/reservation required.,1%; LED series resistor.; rated voltage V: 50; tolerance %: 1; rated power W: 0.0625; maximum body height mm: 0.4

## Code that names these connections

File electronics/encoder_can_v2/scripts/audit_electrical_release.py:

"""Independent pin/function and release checks against reviewed datasheet pinouts.

Run with KiCad Python. Expected package functions are transcribed from primary
sources, separately from electrical_spec.json and the custom schematic symbols.
This is not a model of oscillator startup, EMC, Hall accuracy or real assembly.
"""
import datetime
from pathlib import Path
import json,hashlib,math,re
import pcbnew as p
from schematic_sexpr import parse,get,nodes,pins
R=Path(__file__).resolve().parents[1];b=p.LoadBoard(str(R/'encoder_can_v2.kicad_pcb'));fps={f.GetReference():f for f in b.GetFootprints()}
sch=parse((R/'encoder_can_v2.kicad_sch').read_text());libs={s[1]:s for s in nodes(get(sch,'lib_symbols'),'symbol')};instances={next(q[2] for q in nodes(s,'property') if q[1]=='Reference'):s for s in nodes(sch,'symbol')}
spec=json.loads((R/'design/electrical_spec.json').read_text());cs={c['ref']:c for c in spec['components']};checks=[]
def check(name,condition,detail):
 assert condition,(name,detail)
 checks.append(dict(check=name,passed=True,detail=detail))

def xy(v):return [p.ToMM(v.x),p.ToMM(v.y)]

functions={
 'U1':dict(zip(map(str,range(1,34)),['VDD','PF0','PF1','PG10','PA0','PA1','PA2','PA3','PA4','PA5','PA6','PA7','PB0','VSSA','VDDA','VSS','VDD','PA8','PA9','PA10','PA11','PA12','PA13','PA14','PA15','PB3','PB4','PB5','PB6','PB7','PB8','VSS','VSS'])),
 'U2':dict(zip(map(str,range(1,7)),['SCL','GND','TEST','VCC','INT','SDA'])),
 'U3':dict(zip(map(str,range(1,7)),['SCL','GND','TEST','VCC','INT','SDA'])),
 'U4':dict(zip(map(str,range(1,9)),['TXD','GND','VCC','RXD','NC','CANL','CANH','NC'])),
 'U5':dict(zip(map(str,range(1,6)),['IN','GND','EN','NC','OUT']))}
for ref,expected in functions.items():
 lib=libs[get(instances[ref],'lib_id')[1]];actual={get(q,'number')[1]:get(q,'name')[1] for q in pins(lib)}
 norm=lambda s:re.sub('[^A-Z0-9]','',s.upper())
 check(ref+' package pin functions',set(actual)==set(expected) and all(norm(v) in norm(actual[n]) for n,v in expected.items()),dict(actual=actual,expected=expected))

# These are intended connections, independently checked by physical pad number.
required={
 'U1':{'1':'+3V3','2':'HSE_IN','3':'HSE_OUT','4':'NRST','5':'INT_INNER','6':'INT_OUTER','9':'LED_CMD','10':'LED_PHASE','14':'GND','15':'+3V3','16':'GND','17':'+3V3','18':'I2C2_SDA','19':'I2C2_SCL','21':'CAN_RX','22':'CAN_TX','23':'SWDIO','24':'SWCLK','25':'I2C1_SCL','30':'I2C1_SDA','31':'BOOT0','32':'GND','33':'GND'},
 'U2':{'1':'I2C1_SCL','2':'GND','3':'GND','4':'+3V3','5':'INT_INNER','6':'I2C1_SDA'},
 'U3':{'1':'I2C2_SCL','2':'GND','3':'GND','4':'+3V3','5':'INT_OUTER','6':'I2C2_SDA'},
 'U4':{'1':'CAN_TX','2':'GND','3':'+3V3','4':'CAN_RX','6':'CAN_L','7':'CAN_H'},
 'U5':{'1':'+5V','2':'GND','3':'+5V','5':'+3V3'},
 'D1':{'1':'CAN_H','2':'CAN_L','3':'GND'},'Y1':{'1':'HSE_IN','2':'GND','3':'HSE_OUT','4':'GND'},
 'J1':{'1':'+5V','2':'GND','3':'CAN_H','4':'CAN_L'},'J2':{'1':'+5V','2':'GND','3':'SWDIO','4':'SWCLK','5':'NRST'}}
for ref,expected in required.items():
 actual={q.GetNumber():q.GetNetname() for q in fps[ref].Pads() if q.GetNumber()}
 check(ref+' physical pad nets',all(actual[n]==net for n,net in expected.items()),expected)
for ref,numbers in [('U4',['5','8']),('U5',['4'])]:
 actual={q.GetNumber():q.GetNetname() for q in fps[ref].Pads()}
 check(ref+' NC pads',all(actual[n].startswith('unconnected-') for n in numbers),numbers)
check('Unchanged Hall footprints',all(cs[r]['mpn']=='TMAG5273A2QDBVR' for r in ['U2','U3']),{r:cs[r]['mpn'] for r in ['U2','U3']})
check('Exact crystal',cs['Y1']['mpn']=='ABM10-16.000MHZ-12-R80-3-D30-T' and all(cs[r]['value']=='18pF' for r in ['C13','C14']),dict(mpn=cs['Y1']['mpn'],load_caps_pf=18))
check('Optional CAN termination',cs['R9']['dnp'] and fps['R9'].IsDNP() and cs['R9']['value']=='120','Only two bus ends may be terminated')

bypass={r:c for r,c in [('C1','100nF'),('C2','100nF'),('C3','4.7uF'),('C4','10nF'),('C5','1uF'),('C6','100nF'),('C7','100nF'),('C8','100nF'),('C9','1uF'),('C10','4.7uF'),('C11','4.7uF'),('C12','100nF')]}
check('Bypass/reset capacitor values',all(cs[r]['value']==val for r,val in bypass.items()),bypass)
check('Supply and reset constraints',all(cs[r]['value']=='2.2k' for r in ['R1','R2','R3','R4']) and all(cs[r]['value']=='10k' for r in ['R5','R6','R7','R8']),dict(i2c_pullups_ohm=2200,reset_irq_boot_ohm=10000))

leds=[]
for ref in ['D2','D3','D4']:
 f=fps[ref];pads={q.GetNumber():q for q in f.Pads()};a,z=pads['1'],pads['2'];sizes=[xy(q.GetSize()) for q in [a,z]];pitch=math.dist(xy(a.GetPosition()),xy(z.GetPosition()))
 areas=[]
 for q in [a,z]:
  w,h=xy(q.GetSize());mx,my=xy(q.GetSolderPasteMargin(p.B_Cu));areas.append((w+2*mx)*(h+2*my)/(w*h))
 check(ref+' Kingbright lands',all(abs(sz[0]-.7)<1e-6 and abs(sz[1]-.5)<1e-6 for sz in sizes) and abs(pitch-.9)<2e-6 and all(abs(x-.8)<1e-4 for x in areas),dict(pad_size_mm=sizes,pitch_mm=pitch,paste_area_ratios=areas,cathode_net=a.GetNetname()))
 leds.append(dict(ref=ref,rotation_deg=f.GetOrientationDegrees(),position_mm=xy(f.GetPosition()),cathode_pad=1,anode_pad=2))
check('LED series resistors',all(cs[r]['value']=='1k' for r in ['R10','R11','R12']),dict(max_current_per_channel_at_zero_vf_ma=3.3495/990*1000,max_resistor_power_w=3.3495**2/990))
ep=next(q for q in fps['U1'].Pads() if q.GetNumber()=='33');windows=[q for q in fps['U1'].Pads() if not q.GetNumber() and q.IsOnLayer(p.B_Paste)]
window_sizes=[xy(q.GetSize()) for q in windows];paste_area=sum(w*h-(4-math.pi)*p.ToMM(q.GetRoundRectCornerRadius())**2 for q,(w,h) in zip(windows,window_sizes));ep_area=math.prod(xy(ep.GetSize()))
check('MCU thermal pad paste coverage',len(windows)==9 and all(abs(w-.9)<1e-6 and abs(h-.9)<1e-6 for w,h in window_sizes) and ep.GetNetname()=='GND' and .5<paste_area/ep_area<.8,dict(copper_mm2=ep_area,paste_mm2=paste_area,paste_windows=len(windows),coverage_ratio=paste_area/ep_area))
report=dict(date=datetime.date.today().isoformat(),source_pcb_sha256=hashlib.sha256((R/'encoder_can_v2.kicad_pcb').read_bytes()).hexdigest(),checks=checks,led_assembly=leds,derived=dict(logic_supply_with_1p5pct_tolerance_v=[3.3*.985,3.3*1.015],i2c_capacitance_budget_at_300ns_pf=.3e-6/(.8473*2200*1.01)*1e12,ldo_peak_dissipation_at_5p5V_150mA_w=(5.5-3.3)*.15),sources=['https://www.st.com/resource/en/datasheet/stm32g431kb.pdf','https://www.ti.com/lit/ds/symlink/tmag5273.pdf','https://www.ti.com/lit/ds/symlink/tcan332g.pdf','https://www.ti.com/lit/ds/symlink/tps7a20.pdf','https://assets.nexperia.com/documents/data-sheet/PESD5V0S2BT.pdf','https://www.kingbrightusa.com/images/catalog/SPEC/APG1005SYC-T.pdf'],limits=['Pin/function checks are based on reviewed primary documentation; not device simulation.','C13/C14 are initial load values; oscillator safety factor and drive level need hardware characterization.','64mA average is a planning estimate. Check actual power and thermals; 150mA is a qualification budget.','I2C bus capacitance, CAN immunity, power sequencing and magnetic accuracy are not measured here.'])
(R/'design/electrical_release_audit.json').write_text(json.dumps(report,ensure_ascii=False,indent=2)+'\n');print('Independent electrical release checks:',len(checks),'passed')

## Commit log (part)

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2025-10-19 Update Dockerfile
2025-10-20 fix sep
2025-10-21 make separator
2025-10-21 fix1
2025-10-21 fix2
2025-10-21 fix3
2025-10-21 fix4
2025-10-23 add cap
2025-10-26 add ecc shaft
2025-10-27 add simple cap
2025-10-27 add motor cover
2025-10-28 fix B pos
2025-11-17 eccentric_shaft
2025-11-19 its work
2025-11-23 bracescap_with_bracing
2025-11-24 connector_clamp
2025-11-28 **Title:** Добавлено подробное описание генерируемых деталей в README.md
    - Updated `README.md`: Добавлен раздел "Генерируемые детали" с описанием 11 основных компонентов, включая функции и ключевые характеристики каждой детали
    - Updated `README.md`: Добавлены детализированные сведения о подшипниках, винтах и крепёжных элементах, используемых в сборке
    - Updated `README.md`: Улучшена структура документации с акценто
2025-12-03 shoulder
2025-12-05 hips
2025-12-07 leg kinematics
2025-12-17 encoder
2026-01-07 add config
2026-01-10 body
2026-01-10 shtift&wall
